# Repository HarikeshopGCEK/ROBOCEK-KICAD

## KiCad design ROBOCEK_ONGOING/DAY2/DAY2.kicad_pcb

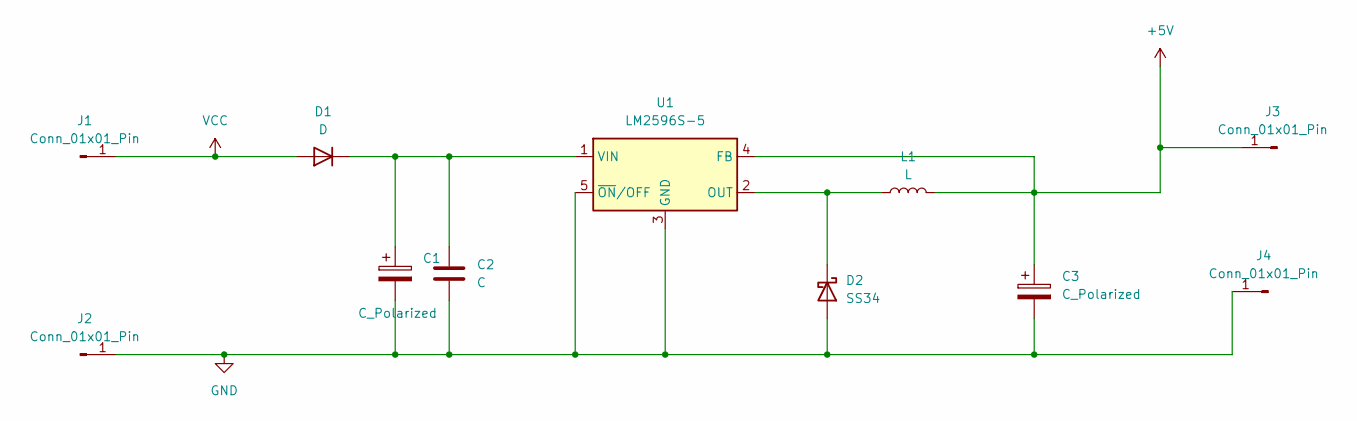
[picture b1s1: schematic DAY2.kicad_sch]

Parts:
C1, C3: C_Polarized; CP_Elec_3x5.3
C2: C; C_0201_0603Metric
D1: D; D_0603_1608Metric
D2: SS34; D_SMA
J1, J2, J3, J4: Conn_01x01_Pin; SolderWire-0.1sqmm_1x01_D0.4mm_OD1mm
L1: L; L_12x12mm_H4.5mm
U1: LM2596S-5; TO-263-5_TabPin3

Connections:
+5V: C3.1, J3.1 (Pin_1_1), L1.2, U1.4 (FB)
GND: C1.2, C2.2, C3.2, D2.2 (A), J2.1 (Pin_1_1), J4.1 (Pin_1_1), U1.3 (GND), U1.5 (~ON/OFF)
unnamed: C1.1, C2.1, D1.1 (K), U1.1 (VIN)
unnamed: D2.1 (K), L1.1, U1.2 (OUT)
VCC: D1.2 (A), J1.1 (Pin_1_1)

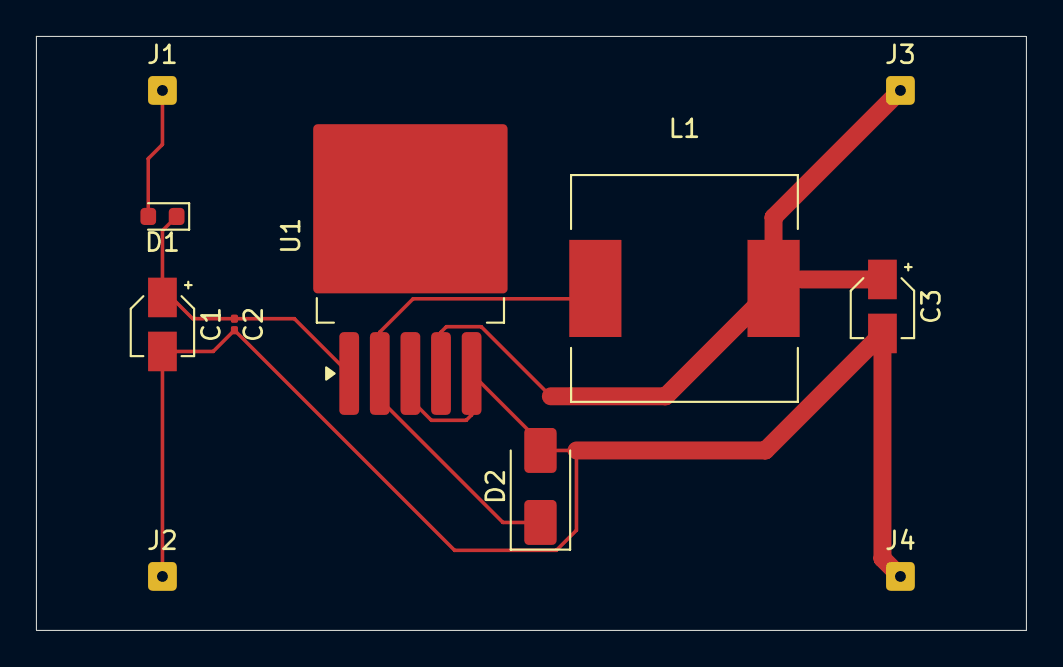
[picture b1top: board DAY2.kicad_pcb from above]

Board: 2 copper layers, 55.0 x 33.0 mm, 11 parts (0 on the bottom side), 5 nets.

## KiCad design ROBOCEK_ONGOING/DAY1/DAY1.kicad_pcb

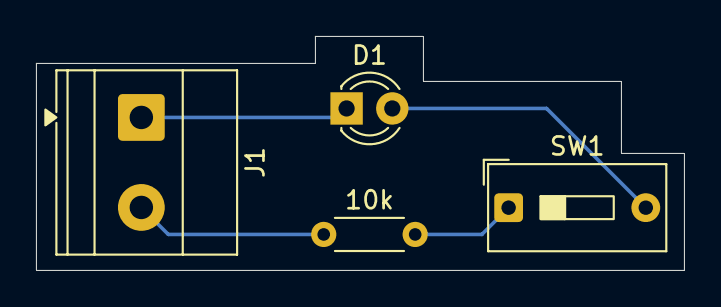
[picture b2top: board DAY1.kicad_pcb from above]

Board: 2 copper layers, 36.0 x 13.0 mm, 4 parts (0 on the bottom side), 4 nets.

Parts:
10k: R; R_Axial_DIN0204_L3.6mm_D1.6mm_P5.08mm_Horizontal
D1: LED; LED_D3.0mm
J1: Power; TerminalBlock_Phoenix_MKDS-1,5-2_1x02_P5.00mm_Horizontal
SW1: SW_SPST; SW_DIP_SPSTx01_Slide_9.78x4.72mm_W7.62mm_P2.54mm

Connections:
+5V: 10k.1, J1.2
GND: D1.1 (K), J1.1
unnamed: D1.2 (A), SW1.2 (B)
unnamed: 10k.2, SW1.1 (A)
